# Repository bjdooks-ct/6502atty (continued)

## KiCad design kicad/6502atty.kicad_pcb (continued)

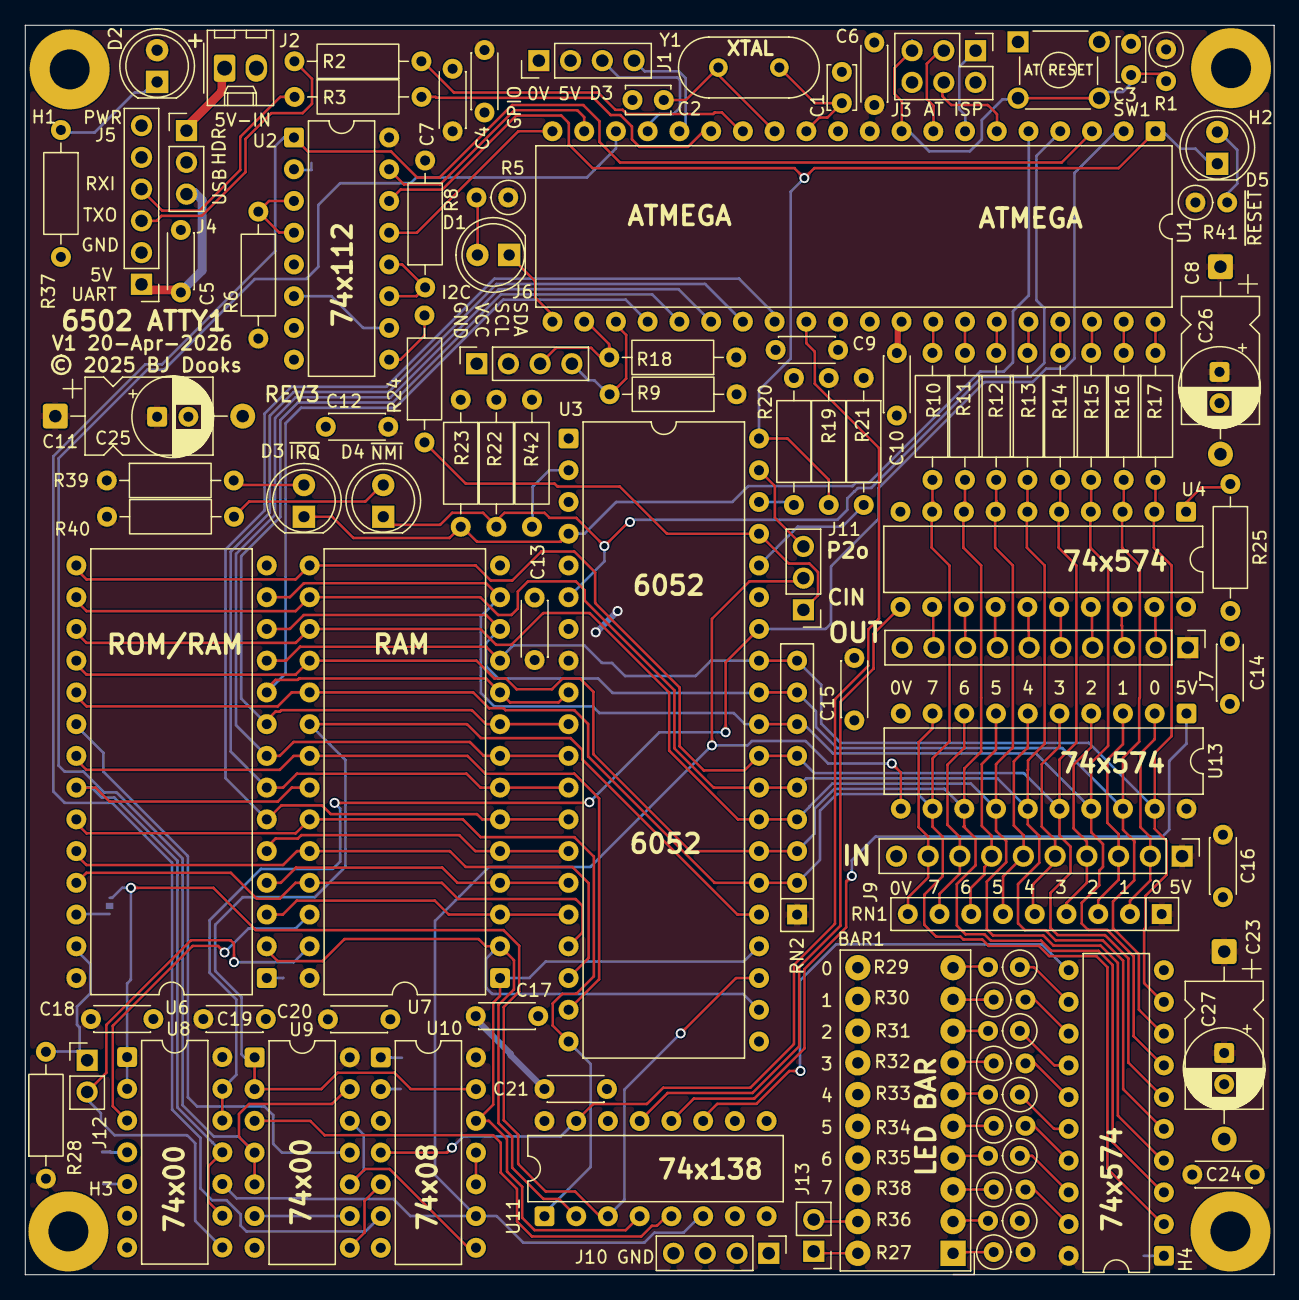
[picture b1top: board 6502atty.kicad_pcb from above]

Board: 2 copper layers, 100.0 x 100.0 mm, 104 parts (1 on the bottom side), 127 nets.

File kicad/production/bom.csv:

Designator,Footprint,Quantity,Value,LCSC Part #
BAR1,HDSP-4850,1,HDSP-4850,
"C1, C2",C_Disc_D3.4mm_W2.1mm_P2.50mm,2,12pF,
C10,C_Disc_D4.3mm_W1.9mm_P5.00mm,1,~,
"C11, C23, C8",CP_Axial_L10.0mm_D6.0mm_P15.00mm_Horizontal,3,100uF/16V,
"C12, C13, C14, C15, C16, C17, C18, C19, C20, C21, C24, C4, C5, C6, C7, C9",C_Disc_D4.3mm_W1.9mm_P5.00mm,16,100nF,
C3,C_Disc_D3.4mm_W2.1mm_P2.50mm,1,?,
D1,LED_D5.0mm,1,LED_Small_Filled,
"D2, D3, D4, D5",LED_D5.0mm,4,RED,
"J1, J10",PinHeader_1x04_P2.54mm_Vertical,2,Conn_01x04_Pin,
"J11, J4, J8",PinHeader_1x03_P2.54mm_Vertical,3,Conn_01x03_Pin,
J12,PinHeader_1x02_P2.54mm_Vertical,1,Conn_01x02_Pin,
J2,Molex_KK-254_AE-6410-02A_1x02_P2.54mm_Vertical,1,Conn_01x02_Pin,
J3,PinHeader_2x03_P2.54mm_Vertical,1,Conn_02x03_Odd_Even,
J5,PinHeader_1x06_P2.54mm_Vertical,1,Conn_01x06_Pin,
J6,PinSocket_1x04_P2.54mm_Vertical,1,Conn_01x04_Pin,
"J7, J9",PinHeader_1x10_P2.54mm_Vertical,2,Conn_01x10_Pin,
R1,R_Axial_DIN0207_L6.3mm_D2.5mm_P2.54mm_Vertical,1,10K,
"R10, R11, R12, R13, R14, R15, R16, R17",R_Axial_DIN0207_L6.3mm_D2.5mm_P10.16mm_Horizontal,8,330R,
"R18, R19, R20, R21, R22, R23, R25, R26, R28, R6, R8, R9",R_Axial_DIN0207_L6.3mm_D2.5mm_P10.16mm_Horizontal,12,4K7,
"R2, R3, R37, R39, R40, R5",R_Axial_DIN0207_L6.3mm_D2.5mm_P10.16mm_Horizontal,6,1K,
R24,R_Axial_DIN0207_L6.3mm_D2.5mm_P10.16mm_Horizontal,1,560R,
"R27, R29, R30, R31, R32, R33, R34, R35, R38",R_Axial_DIN0207_L6.3mm_D2.5mm_P2.54mm_Vertical,9,680R,
R41,R_Axial_DIN0207_L6.3mm_D2.5mm_P2.54mm_Vertical,1,1K,
R42,R_Axial_DIN0207_L6.3mm_D2.5mm_P10.16mm_Horizontal,1,R,
RN1,R_Array_SIP9,1,R_Network08,
SW1,SW_TH_Tactile_Omron_B3F-10xx,1,SW_Push,
U1,DIP-40_W15.24mm,1,ATmega164P-20P,
U10,DIP-14_W7.62mm,1,74LS08,
U11,DIP-16_W7.62mm,1,74LS138,
"U12, U4",DIP-20_W7.62mm,2,74LS574,
U2,DIP-16_W7.62mm,1,74LS112,
U3,DIP-40_W15.24mm,1,W65C02SxP,
U5,DIP-20_W7.62mm,1,74HC245,
U6,DIP-28_W15.24mm,1,27C128,
U7,DIP-28_W15.24mm,1,KM62256CLP,
"U8, U9",DIP-14_W7.62mm,2,74LS00,
Y1,Crystal_HC49-4H_Vertical,1,18.432MHz,

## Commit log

2026-03-25 firmware: minor changes for include, change download code
2026-03-25 target_asm: fixup makefile, rename headers
2026-03-25 readme updates, added photo album and revision ntoes
2026-03-25 pcb: move around stuff to make pcb smaller
2026-03-25 docs: add new pcb view
2026-03-25 pcb: run production output
2026-03-25 pcb: minor schematic updates
2026-03-25 update readme with clock logic and rev2 notes
2026-03-25 pcb: minor routing fixes, add rjek's bee
2026-03-25 pcb: silkscreen updates, minor routing updates
2026-03-25 v1_r2 production data
2026-03-26 pcb: fix value of RN1
    also accidentally pushed release2 data
2026-03-26 add note about bee logo
2026-03-27 fix path to main picture
2026-03-31 start notes on rev3
2026-04-02 start of rev3, reduce x-size, leds consistent
2026-04-02 missing save commited
2026-04-02 routing fixes and make teardrops slightly smaller
2026-04-13 readme updates
2026-04-13 updates for moving pcb stuff around
2026-04-13 more movement/updates
2026-04-17 firmware: spelling fix
2026-04-17 firmware: merge shift an and
2026-04-17 firmware: cleanup ISR vector
2026-04-17 kicad: routing and board updates
2026-04-17 firmware: add option to output square-ish wave
2026-04-17 firmware: rename _th to _bin
2026-04-17 firmware: add simple write-to-register
2026-04-17 firmware: move code around, use 'null test' for debug
2026-04-17 firmware: add comment about timer, go back to string test
2026-04-17 firmware: make IO 0x1C just call putbyte direct
    no point in getting pf() involved with a very simple print
2026-04-17 firmware: add initial device register map
2026-04-23 remove lock file from kicad
    this file should never have been added to the repo, so remove it
2026-04-23 update to kicad10, v1_r3 release
2026-04-23 firmware: add null test output
2026-04-23 ignore backups
2026-04-23 ignore kicad lock files
2026-04-23 updated to use 74x574 for input, then drc fixes
2026-04-23 readme: updates for v1_r3
2026-04-24 pcb: updated silkscreen bits
2026-04-27 kicad: v1_rev3 production
2026-04-27 fixup readme for release3
